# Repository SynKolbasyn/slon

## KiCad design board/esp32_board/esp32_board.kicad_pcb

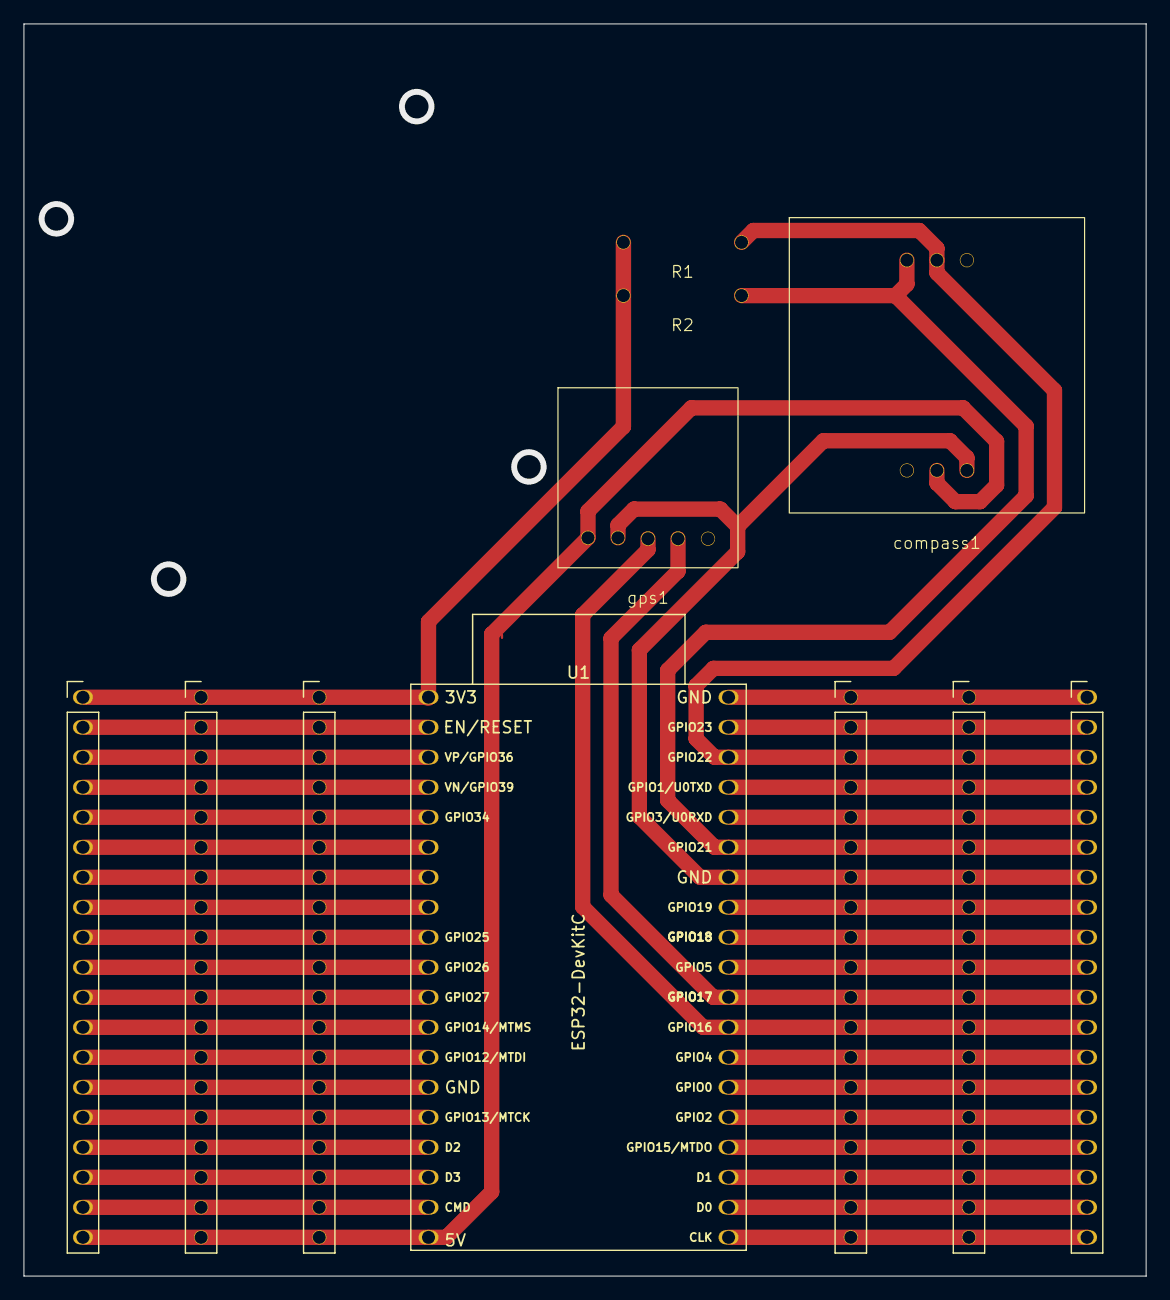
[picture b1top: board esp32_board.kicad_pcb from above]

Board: 2 copper layers, 95.0 x 106.0 mm, 11 parts (0 on the bottom side), 36 nets.

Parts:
J1, J2: Screw_Terminal_01x19; PinHeader_1x19_P2.54mm_Vertical
J3, J5: Conn_01x19_Socket; PinHeader_1x19_P2.54mm_Vertical
J4, J6: Conn_01x19_Pin; PinHeader_1x19_P2.54mm_Vertical
R1, R2: 2200; r
U1: ESP32-DevKitC
compass1: compass
gps1: gps

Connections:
0: J1.14, J5.14, J6.14, U1.25 (GPIO0/BOOT/ADC2_CH1)
2: J1.15, J5.15, J6.15, U1.24 (ADC2_CH2/GPIO2)
3V3: J2.1, J3.1, J4.1, R1.1, R2.1, U1.1 (3V3)
4: J1.13, J5.13, J6.13, U1.26 (ADC2_CH0/GPIO4)
5: J1.10, J5.10, J6.10, U1.29 (GPIO5)
12: J2.13, J3.13, J4.13, U1.13 (MTDI/GPIO12/ADC2_CH5)
13: J2.15, J3.15, J4.15, U1.15 (MTCK/GPIO13/ADC2_CH4)
14: J2.12, J3.12, J4.12, U1.12 (MTMS/GPIO14/ADC2_CH6)
15: J1.16, J5.16, J6.16, U1.23 (MTDO/GPIO15/ADC2_CH3)
16: J1.12, J5.12, J6.12, U1.27 (GPIO16), gps1.3 (TX)
17: J1.11, J5.11, J6.11, U1.28 (GPIO17), gps1.4 (RX)
18: J1.9, J5.9, J6.9, U1.30 (GPIO18)
19: J1.8, J5.8, J6.8, U1.31 (GPIO19)
21: J1.6, J5.6, J6.6, R2.2, U1.33 (GPIO21), compass1.4 (D)
22: J1.3, J5.3, J6.3, R1.2, U1.36 (GPIO22), compass1.5 (C)
23: J1.2, J5.2, J6.2, U1.37 (GPIO23)
25: J2.9, J3.9, J4.9, U1.9 (DAC_1/ADC2_CH8/GPIO25)
26: J2.10, J3.10, J4.10, U1.10 (DAC_2/ADC2_CH9/GPIO26)
27: J2.11, J3.11, J4.11, U1.11 (ADC2_CH7/GPIO27)
32: J2.7, J3.7, J4.7, U1.7 (32K_XP/GPIO32/ADC1_CH4)
33: J2.8, J3.8, J4.8, U1.8 (32K_XN/GPIO33/ADC1_CH5)
34: J2.5, J3.5, J4.5, U1.5 (VDET_1/GPIO34/ADC1_CH6)
35: J2.6, J3.6, J4.6, U1.6 (VDET_2/GPIO35/ADC1_CH7)
CLK: J1.19, J5.19, J6.19, U1.20 (SD_CLK/GPIO6)
CMD: J2.18, J3.18, J4.18, U1.18 (CMD)
EN: J2.2, J3.2, J4.2, U1.2 (CHIP_PU)
GND: J1.1, J1.7, J2.14, J3.14, J4.14, J5.1, J5.7, J6.1, J6.7, U1.14 (GND), U1.32 (GND), U1.38 (GND), compass1.3 (G), gps1.2 (GND)
RX: J1.5, J5.5, J6.5, U1.34 (U0RXD/GPIO3)
SD0: J1.18, J5.18, J6.18, U1.21 (SD_DATA0/GPIO7)
SD1: J1.17, J5.17, J6.17, U1.22 (SD_DATA1/GPIO8)
SD2: J2.16, J3.16, J4.16, U1.16 (SD_DATA2/GPIO9)
SD3: J2.17, J3.17, J4.17, U1.17 (SD_DATA3/GPIO10)
SN: J2.4, J3.4, J4.4, U1.4 (SENSOR_VN/GPIO39/ADC1_CH3)
SP: J2.3, J3.3, J4.3, U1.3 (SENSOR_VP/GPIO36/ADC1_CH0)
TX: J1.4, J5.4, J6.4, U1.35 (U0TXD/GPIO1)
V5: J2.19, J3.19, J4.19, U1.19 (5V), compass1.2 (V), gps1.1 (VCC)

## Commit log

2022-10-17 v0.0.0 Нулевая версия, в ней ничего нет, просто пустой прект
2022-10-17 v0.1.0 Добавлен интерфейс
2022-10-17 v0.1.1 Небольшие изменения в build.gradle(:app)
2022-10-17 v0.2.0 Добавлен GPS
2022-10-21 v0.2.1 Добавлено обновление activity
2023-09-27 feat(ros): Added "slon" pakage and configured "package.xml"
2023-09-27 feat(ros): Added "main_node" and configured "CMakeLists.txt" for slon pakage
2023-09-27 feat(ros): Added OpenCV QR code detection
2023-09-28 feat(esp): Added Esp32 and simple ros control
2023-09-28 feat(esp): Added "Free RTOS"
2023-09-28 feat(ros): Added test node
2023-09-30 feat(esp): Added tetrix driver library
2023-09-30 fix: Fixed robot control and qr code detection
2023-10-06 feat(esp): Added GPS
2023-10-06 feat(android): Added bluetooth devices list and enabling bluetooth
2023-10-09 feat(bt): Added bluetooth to android app and esp32
2023-10-10 feat(esp): Added compass
2023-11-16 feat(compass): Compass works but net more tests
2023-11-19 feat(ros): Ros works. All works. BUT COMPASS DONT WORK
2023-11-19 feat(compass): COMPASS WORKS!!! not very well, but works
2023-11-23 fix(bt): Fixed some bugs with bluetooth
2023-11-23 fix(proj): Fixed VERY MUTCH BUGS
2023-11-23 feat(app): The android app has been completed
2023-11-28 feat(mv): Added machime vision for qr code detection
2024-02-05 feat: added ctl startup
2024-02-05 feat: added sprayer
2024-02-05 fix: fixed distance recognition
2024-02-14 added aruco detection
2024-02-14 feat: Improved performance
2024-02-14 feat: small changes
2024-02-14 feat:csmall changes
2024-02-15 feat: Added boot sturtup set command
2024-02-15 fix: bug fixed
2024-02-15 fix: bugs fixed
2024-02-15 fix: turn on compass
2024-02-15 feat: ADDED AIR HORN
2024-02-15 fix: added pins for sprayer and horn
2024-02-19 fix: FIXED FATAL ERROR WITH AIR HORN. IT COST ME A CARLOAD OF NERVE CELLS
2024-02-19 fix: fixed pid regulyator
2024-03-17 feat: Added docs and starting create own board
2024-03-17 feat: Updated docs
2024-03-17 feat: Added schematic for board
2024-03-18 feat: Added presentation
2024-03-18 feat: Updated presentation
2024-03-19 feat: Updated board
2024-03-20 feat: Updated presentation and board
2024-03-20 feat: Updated board and presentation
2024-03-25 feat: Added respawn to main.lauch
2024-03-26 feat(board): Added modules - gps, compass, relay. And builded schematic
2024-03-26 fix(board): Removed unused files
2024-03-26 feat(docs): Added board schematic into docs
2024-03-26 feat: Updated docs and board
2024-03-27 feat(board): Added roads
2024-03-27 feat(docs): Added drawings
2024-03-28 feat(board): Updated board
2024-04-10 feat: Final board version and updated docs
